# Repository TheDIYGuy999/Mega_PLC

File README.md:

# This is an Arduino based, modular Industrial PLC

## I have designed this PLC back in 2016. It is currently in use in an industrial screw tightening robot:
- 4 stepper motors for X, Y, Z axes and for screw tightening
- Matrix keyboard
- I2C LCD
- Digital I/O in use for pneumatic screw feeding system, buttons and reference switches

## Features:
- Works wit an Arduino MEGA or DUE
- DO board with 16 24V, 500mA PNP digital outputs, optoinsulated, short circuit protected @ about 900mA
- DI board with 16 24V PNP digital inputs, optoinsulated
- Stepper board for 4 stepper motors, torque adjustable via PWM
- Slot for communication board (I2C, CAN, SPI, 2x Serial)
- Slot for analog board (Analog in, PWM, DAC, I2C)

## This repo contains:
- Eagle schematics
- Eagle board files
- PDF schematics
- The analog and communication boards were made out of perfboard and are NOT included. Maybe someone other is interested in adding them.

## Pictures:

## Videos:
- I/O boards: https://www.youtube.com/watch?v=W2pYYh6aUXc
- First tepper tests: https://www.youtube.com/watch?v=gJDdZBuH5Kc

(c) 2016  TheDIYGuy999

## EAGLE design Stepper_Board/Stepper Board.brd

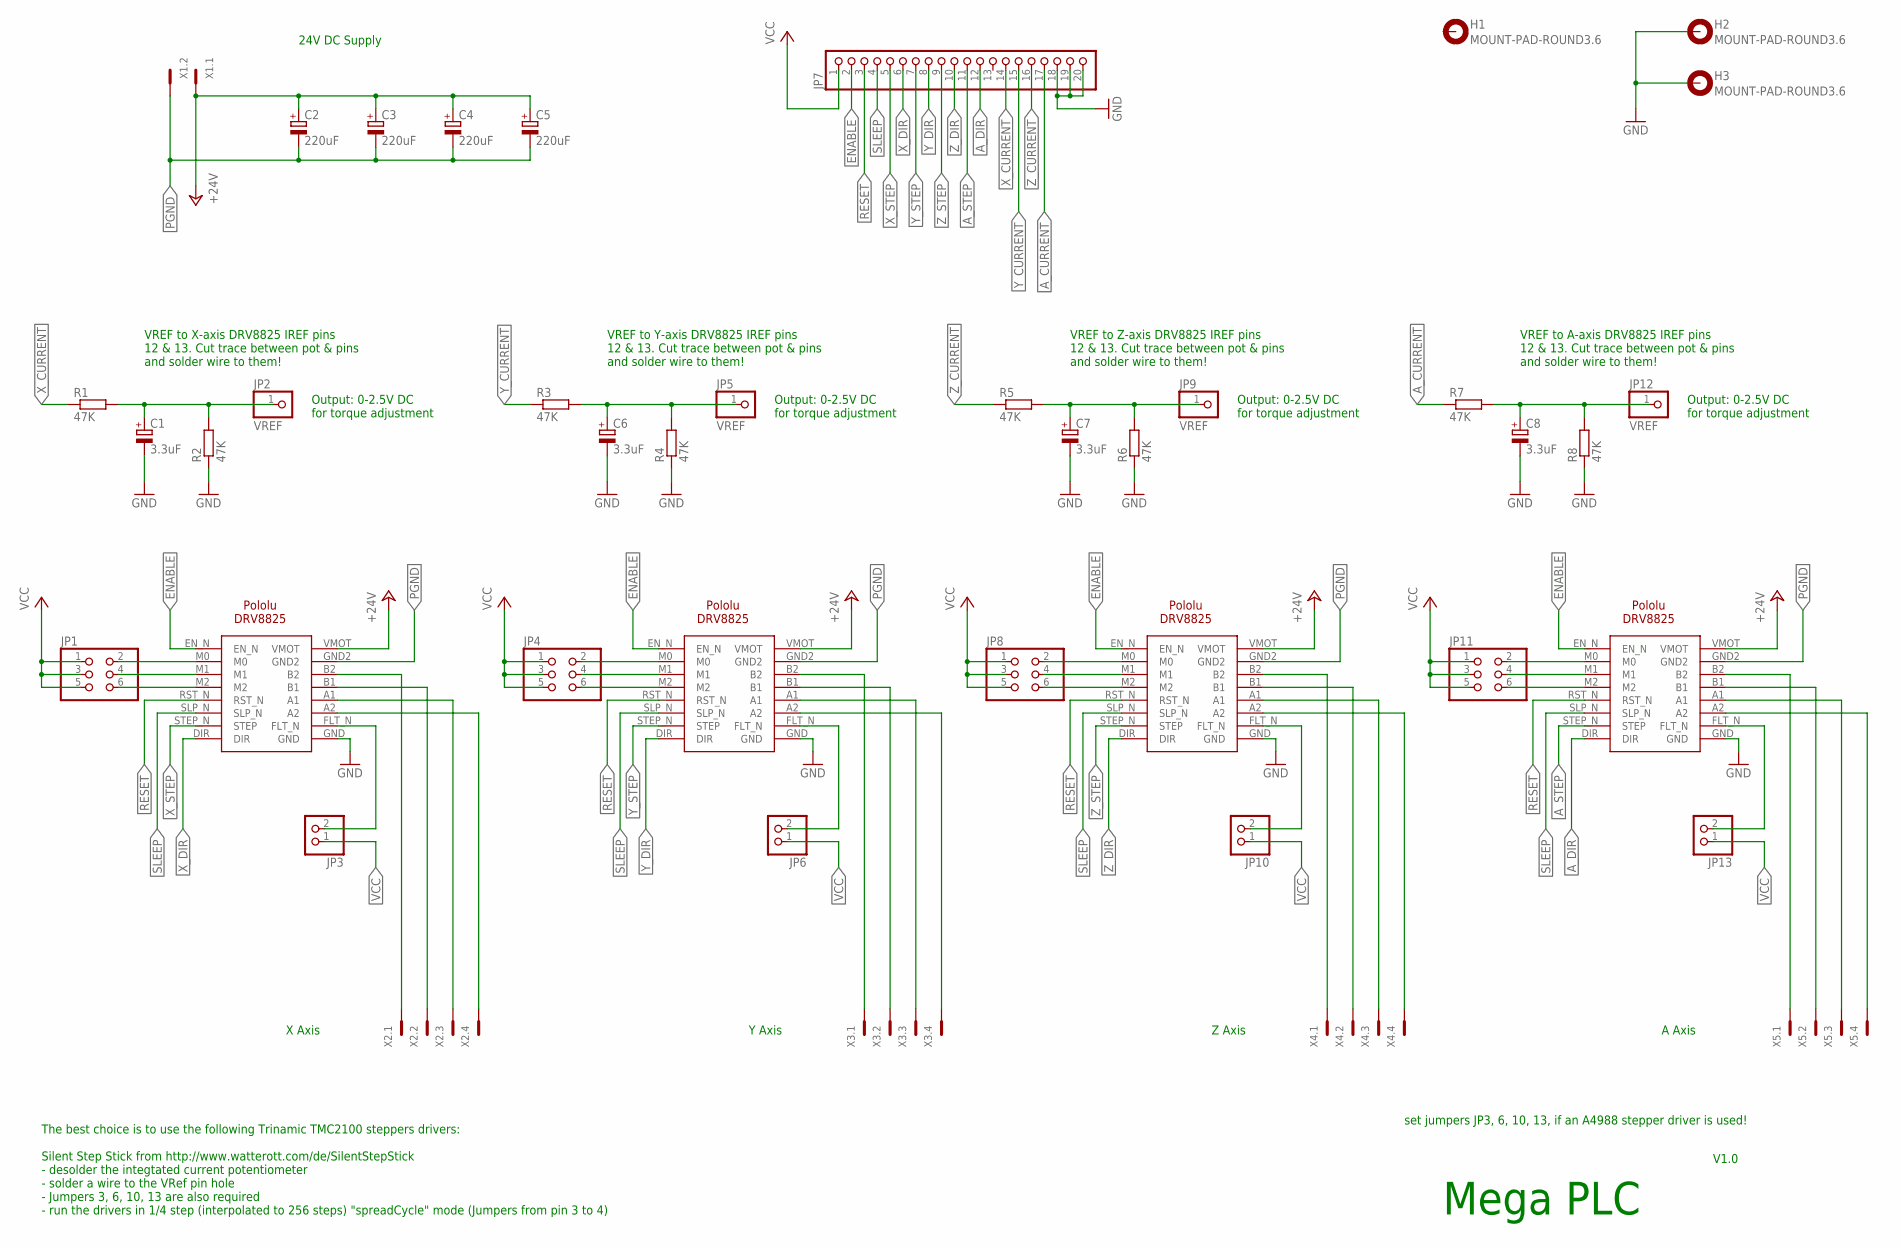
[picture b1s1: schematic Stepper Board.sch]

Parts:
C1, C6, C7, C8: 3.3uF; B45181A
C2, C3, C4, C5: 220uF; E5-10,5
H1, H2, H3: MOUNT-PAD-ROUND3.6; 3,6-PAD
JP1, JP4, JP8, JP11: PINHD-2X3; 2X03
JP2, JP5, JP9, JP12: VREF; 1X01
JP3, JP6, JP10, JP13: PINHD-1X2; 1X02
JP7: PINHD-1X20/90; 1X20/90
R1: 47K; 0204/7
R2, R4, R6, R8: 47K; 0207/15
R3, R5, R7: 47K; 0207/2V
U1, U2, U3, U4: POLOLU-DRV8825
X1: MC2
X2, X3, X4, X5: MC4

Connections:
+24V: C2.+, C3.+, C4.+, C5.+, U1.VMOT, U2.VMOT, U3.VMOT, U4.VMOT, X1.1
A_CURRENT: JP7.17, R7.1
A_DIR: JP7.12, U4.DIR
A_FLT: JP13.2, U4.FLT_N
A_STEP: JP7.11, U4.STEP_N (STEP)
ENABLE: JP7.2, U1.EN_N, U2.EN_N, U3.EN_N, U4.EN_N
GND: C1.-, C6.-, C7.-, C8.-, H2.B3,6, H3.B3,6, JP7.18, JP7.19, JP7.20, R2.1, R4.1, R6.1, R8.1, U1.GND, U2.GND, U3.GND, U4.GND
unnamed: U1.A2, X2.4
unnamed: U1.A1, X2.3
unnamed: JP1.2, U1.M0
unnamed: JP1.4, U1.M1
unnamed: JP1.6, U1.M2
unnamed: U1.B1, X2.2
unnamed: U1.B2, X2.1
unnamed: U2.A2, X3.4
unnamed: U2.A1, X3.3
unnamed: U2.B1, X3.2
unnamed: U2.B2, X3.1
unnamed: U3.A2, X4.4
unnamed: U3.A1, X4.3
unnamed: U3.B1, X4.2
unnamed: U3.B2, X4.1
unnamed: U4.A2, X5.4
unnamed: U4.A1, X5.3
unnamed: U4.B1, X5.2
unnamed: U4.B2, X5.1
unnamed: JP4.2, U2.M0
unnamed: JP4.4, U2.M1
unnamed: JP4.6, U2.M2
unnamed: JP8.2, U3.M0
unnamed: JP8.4, U3.M1
unnamed: JP8.6, U3.M2
unnamed: JP11.2, U4.M0
unnamed: JP11.4, U4.M1
unnamed: JP11.6, U4.M2
unnamed: C8.+, JP12.1, R7.2, R8.2
unnamed: C7.+, JP9.1, R5.2, R6.2
unnamed: C6.+, JP5.1, R3.2, R4.2
unnamed: C1.+, JP2.1, R1.2, R2.2
PGND: C2.-, C3.-, C4.-, C5.-, U1.GND2, U2.GND2, U3.GND2, U4.GND2, X1.2
RESET: JP7.3, U1.RST_N, U2.RST_N, U3.RST_N, U4.RST_N
SLEEP: JP7.4, U1.SLP_N, U2.SLP_N, U3.SLP_N, U4.SLP_N
VCC: JP1.1, JP1.3, JP1.5, JP3.1, JP4.1, JP4.3, JP4.5, JP6.1, JP7.1, JP8.1, JP8.3, JP8.5, JP10.1, JP11.1, JP11.3, JP11.5, JP13.1
X_CURRENT: JP7.14, R1.1
X_DIR: JP7.6, U1.DIR
X_FLT: JP3.2, U1.FLT_N
X_STEP: JP7.5, U1.STEP_N (STEP)
Y_CURRENT: JP7.15, R3.1
Y_DIR: JP7.8, U2.DIR
Y_FLT: JP6.2, U2.FLT_N
Y_STEP: JP7.7, U2.STEP_N (STEP)
Z_CURRENT: JP7.16, R5.1
Z_DIR: JP7.10, U3.DIR
Z_FLT: JP10.2, U3.FLT_N
Z_STEP: JP7.9, U3.STEP_N (STEP)

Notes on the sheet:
24V DC Supply
VREF to A-axis DRV8825 IREF pins 12 & 13. Cut trace between pot & pins and solder wire to them!
X Axis
Y Axis
Z Axis
A Axis
Output: 0-2.5V DC for torque adjustment
Mega PLC
set jumpers JP3, 6, 10, 13, if an A4988 stepper driver is used!
VREF to Z-axis DRV8825 IREF pins 12 & 13. Cut trace between pot & pins and solder wire to them!
VREF to Y-axis DRV8825 IREF pins 12 & 13. Cut trace between pot & pins and solder wire to them!
VREF to X-axis DRV8825 IREF pins 12 & 13. Cut trace between pot & pins and solder wire to them!
V1.0
The best choice is to use the following Trinamic TMC2100 steppers drivers: Silent Step Stick from http://www.watterott.com/de/SilentStepStick - desolder the integtated current potentiometer - solder a wire to the VRef pin hole - Jumpers 3, 6, 10, 13 are also required - run the drivers in 1/4 step (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

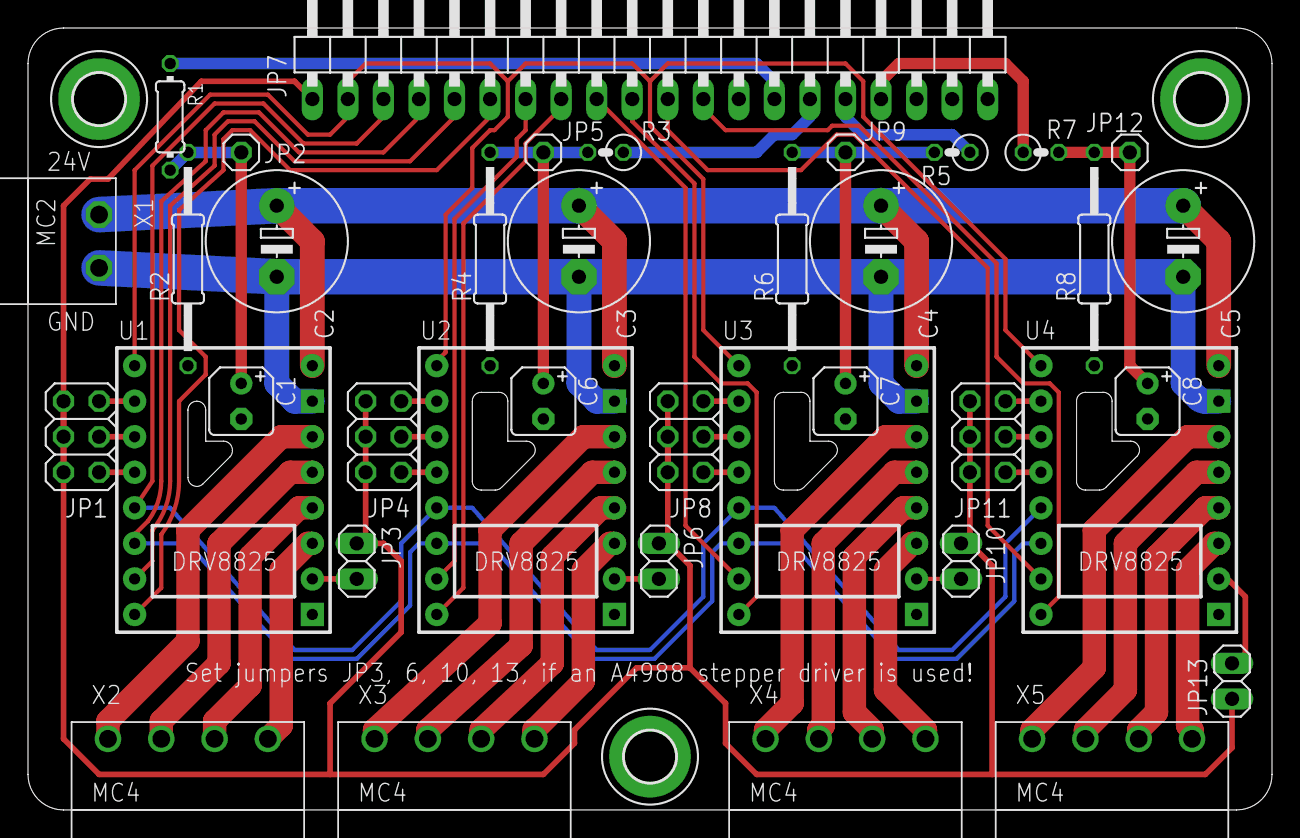
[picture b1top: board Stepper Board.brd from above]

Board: 2 copper layers, 88.9 x 55.9 mm, 41 parts (0 on the bottom side), 55 nets.

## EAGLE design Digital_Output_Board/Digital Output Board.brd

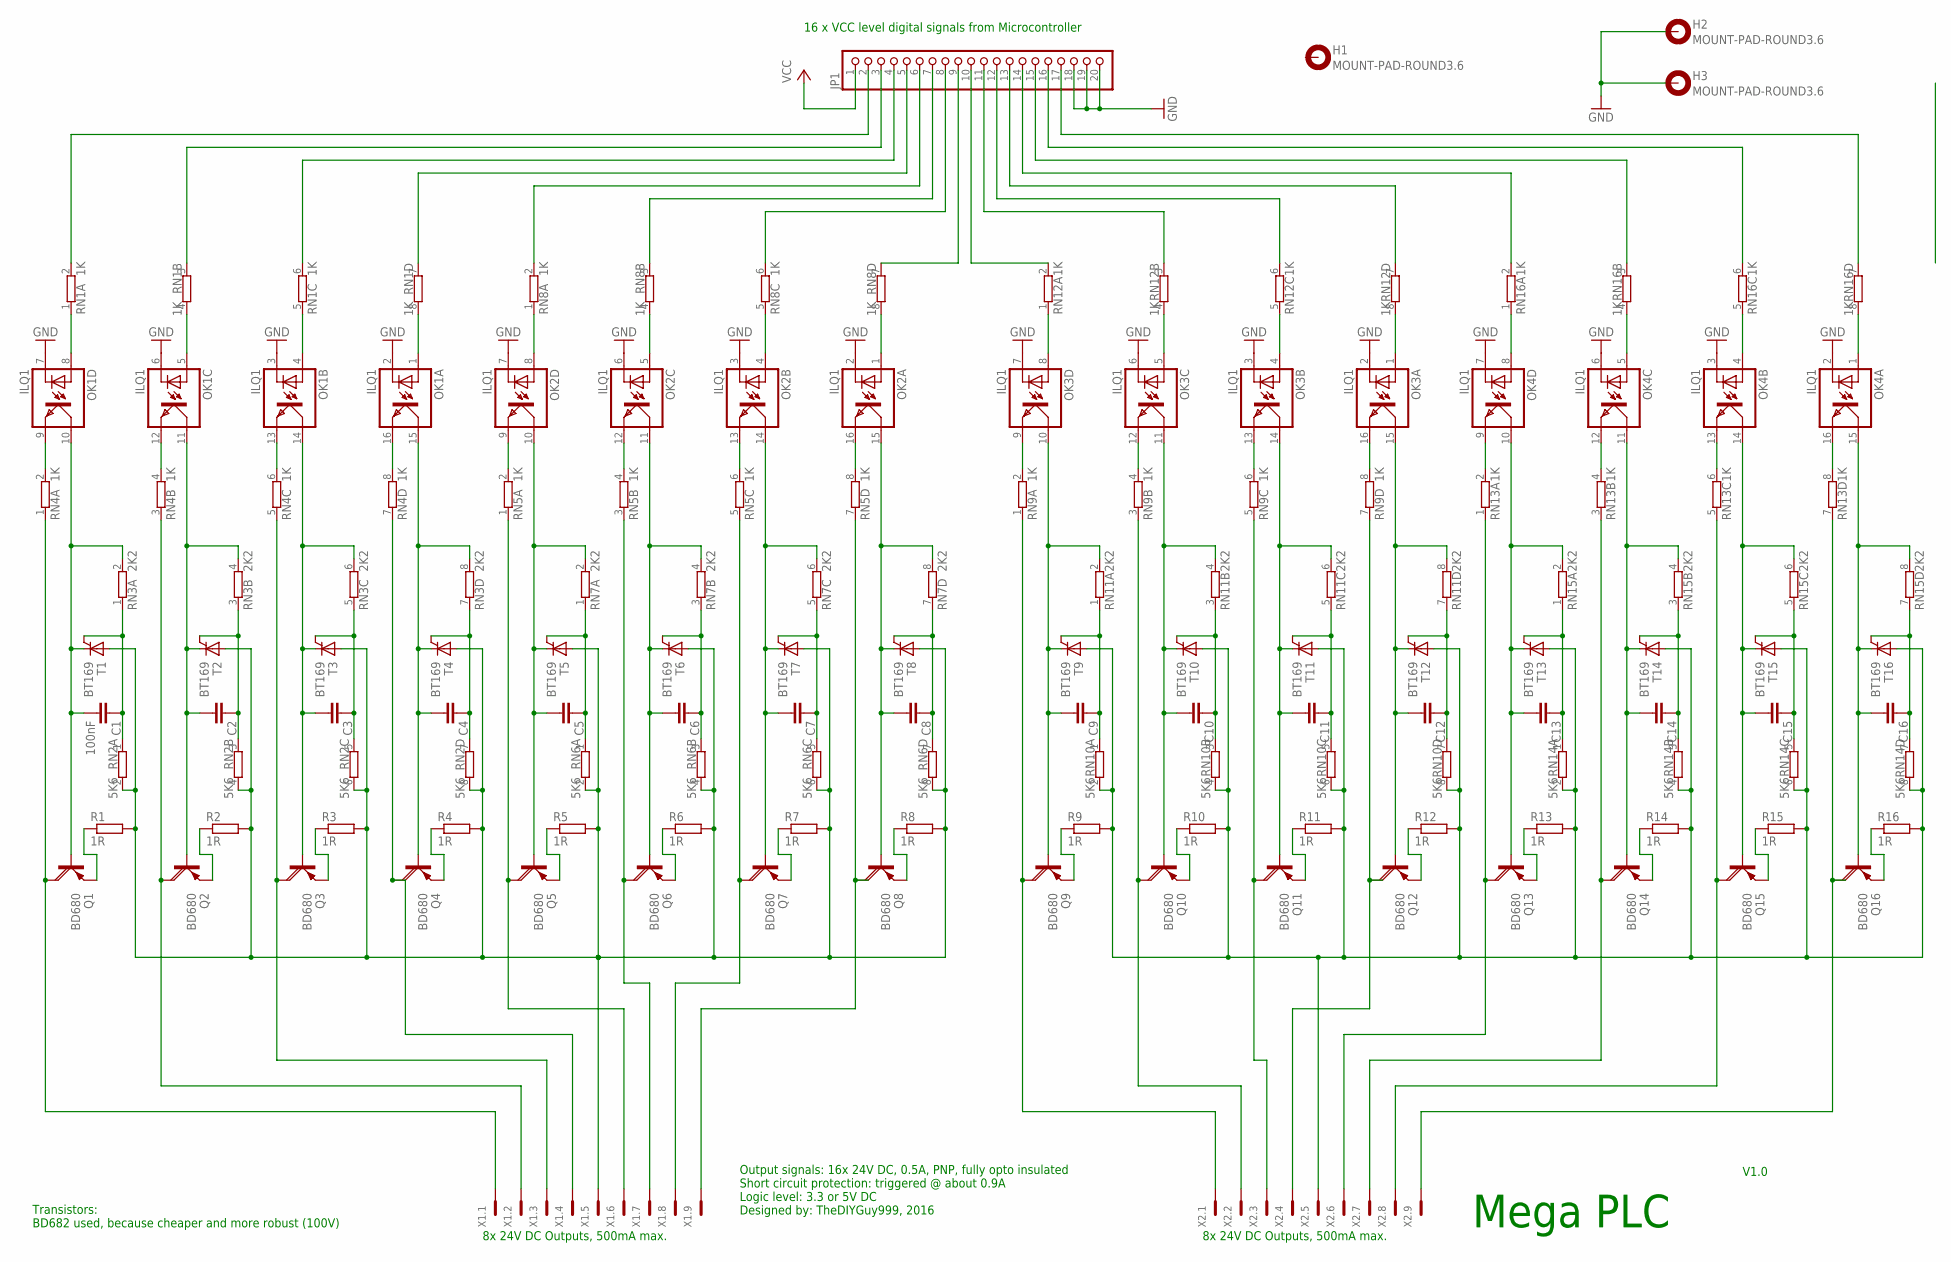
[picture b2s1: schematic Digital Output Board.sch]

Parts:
C1: 100nF; C025-024X044
C2, C3, C4, C5, C6, C7, C8, C9, C10, C11, C12, C13, C14, C15, C16: C-EU025-024X044; C025-024X044
H1, H2, H3: MOUNT-PAD-ROUND3.6; 3,6-PAD
JP1: PINHD-1X20/90; 1X20/90
OK1, OK2, OK3, OK4: ILQ1; DIL16
Q1, Q2, Q3, Q4, Q5, Q6, Q7, Q8, Q9, Q10, Q11, Q12, Q13, Q14, Q15, Q16: BD680; TO126AV
R1, R2, R3, R4, R5, R6, R7, R8, R9, R10, R11, R12, R13, R14, R15, R16: 1R; 0207/10
RN1, RN4, RN5, RN8, RN9, RN12, RN13, RN16: 1K; SIL8
RN2, RN6, RN10, RN14: 5K6; SIL8
RN3, RN7, RN11, RN15: 2K2; SIL8
T1, T2, T3, T4, T5, T6, T7, T8, T9, T10, T11, T12, T13, T14, T15, T16: BT169; TO92-2
X1, X2: MC9

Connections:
C+1: R1.2, R2.2, R3.2, R4.2, R5.2, R6.2, R7.2, R8.2, RN2.2, RN2.4 (2), RN2.6 (2), RN2.8 (2), RN6.2, RN6.4 (2), RN6.6 (2), RN6.8 (2), T1.A, T2.A, T3.A, T4.A, T5.A, T6.A, T7.A, T8.A, X1.5
C+2: R9.2, R10.2, R11.2, R12.2, R13.2, R14.2, R15.2, R16.2, RN10.2, RN10.4 (2), RN10.6 (2), RN10.8 (2), RN14.2, RN14.4 (2), RN14.6 (2), RN14.8 (2), T9.A, T10.A, T11.A, T12.A, T13.A, T14.A, T15.A, T16.A, X2.5
GND: H2.B3,6, H3.B3,6, JP1.18, JP1.19, JP1.20, OK1.2 (C), OK1.3 (C), OK1.6 (C), OK1.7 (C), OK2.2 (C), OK2.3 (C), OK2.6 (C), OK2.7 (C), OK3.2 (C), OK3.3 (C), OK3.6 (C), OK3.7 (C), OK4.2 (C), OK4.3 (C), OK4.6 (C), OK4.7 (C)
unnamed: Q1.E, R1.1
unnamed: OK1.8 (A), RN1.1
unnamed: OK1.5 (A), RN1.4 (2)
unnamed: OK1.4 (A), RN1.5 (1)
unnamed: OK1.1 (A), RN1.8 (2)
unnamed: JP1.2, RN1.2
unnamed: JP1.3, RN1.3 (1)
unnamed: JP1.4, RN1.6 (2)
unnamed: JP1.5, RN1.7 (1)
unnamed: OK1.9 (EMIT), RN4.2
unnamed: OK1.12 (EMIT), RN4.4 (2)
unnamed: OK1.13 (EMIT), RN4.6 (2)
unnamed: OK1.16 (EMIT), RN4.8 (2)
unnamed: C1.2, OK1.10 (COL), Q1.B, RN3.2, T1.C
unnamed: C1.1, RN2.1, RN3.1, T1.G
unnamed: Q1.C, RN4.1, X1.1
unnamed: Q2.C, RN4.3 (1), X1.2
unnamed: Q3.C, RN4.5 (1), X1.3
unnamed: Q4.C, RN4.7 (1), X1.4
unnamed: C2.2, OK1.11 (COL), Q2.B, RN3.4 (2), T2.C
unnamed: C3.2, OK1.14 (COL), Q3.B, RN3.6 (2), T3.C
unnamed: C4.2, OK1.15 (COL), Q4.B, RN3.8 (2), T4.C
unnamed: Q2.E, R2.1
unnamed: Q3.E, R3.1
unnamed: Q4.E, R4.1
unnamed: C2.1, RN2.3 (1), RN3.3 (1), T2.G
unnamed: C3.1, RN2.5 (1), RN3.5 (1), T3.G
unnamed: C4.1, RN2.7 (1), RN3.7 (1), T4.G
unnamed: JP1.6, RN8.2
unnamed: JP1.7, RN8.3 (1)
unnamed: JP1.8, RN8.6 (2)
unnamed: JP1.9, RN8.7 (1)
unnamed: OK2.8 (A), RN8.1
unnamed: OK2.4 (A), RN8.5 (1)
unnamed: OK2.5 (A), RN8.4 (2)
unnamed: OK2.1 (A), RN8.8 (2)
unnamed: OK2.9 (EMIT), RN5.2
unnamed: OK2.12 (EMIT), RN5.4 (2)
unnamed: OK2.13 (EMIT), RN5.6 (2)
unnamed: OK2.16 (EMIT), RN5.8 (2)
unnamed: C5.1, RN6.1, RN7.1, T5.G
unnamed: Q5.E, R5.1
unnamed: C5.2, OK2.10 (COL), Q5.B, RN7.2, T5.C
unnamed: Q5.C, RN5.1, X1.6
unnamed: Q6.C, RN5.3 (1), X1.7
unnamed: Q7.C, RN5.5 (1), X1.8
unnamed: Q8.C, RN5.7 (1), X1.9
unnamed: C6.2, OK2.11 (COL), Q6.B, RN7.4 (2), T6.C
unnamed: C7.2, OK2.14 (COL), Q7.B, RN7.6 (2), T7.C
unnamed: C8.2, OK2.15 (COL), Q8.B, RN7.8 (2), T8.C
unnamed: Q6.E, R6.1
unnamed: Q7.E, R7.1
unnamed: Q8.E, R8.1
unnamed: C6.1, RN6.3 (1), RN7.3 (1), T6.G
unnamed: C7.1, RN6.5 (1), RN7.5 (1), T7.G
unnamed: C8.1, RN6.7 (1), RN7.7 (1), T8.G
unnamed: OK3.8 (A), RN12.1
unnamed: OK3.4 (A), RN12.5 (1)
unnamed: OK3.5 (A), RN12.4 (2)
unnamed: OK3.1 (A), RN12.8 (2)
unnamed: OK3.9 (EMIT), RN9.2
unnamed: OK3.12 (EMIT), RN9.4 (2)
unnamed: OK3.13 (EMIT), RN9.6 (2)
unnamed: OK3.16 (EMIT), RN9.8 (2)
unnamed: C9.1, RN10.1, RN11.1, T9.G
unnamed: Q9.E, R9.1
unnamed: C9.2, OK3.10 (COL), Q9.B, RN11.2, T9.C
unnamed: Q9.C, RN9.1, X2.1
unnamed: Q10.C, RN9.3 (1), X2.2
unnamed: Q11.C, RN9.5 (1), X2.3
unnamed: Q12.C, RN9.7 (1), X2.4
unnamed: C10.2, OK3.11 (COL), Q10.B, RN11.4 (2), T10.C
unnamed: C11.2, OK3.14 (COL), Q11.B, RN11.6 (2), T11.C
unnamed: C12.2, OK3.15 (COL), Q12.B, RN11.8 (2), T12.C
unnamed: Q10.E, R10.1
unnamed: Q11.E, R11.1
unnamed: Q12.E, R12.1
unnamed: C10.1, RN10.3 (1), RN11.3 (1), T10.G
unnamed: C11.1, RN10.5 (1), RN11.5 (1), T11.G
unnamed: C12.1, RN10.7 (1), RN11.7 (1), T12.G
unnamed: OK4.8 (A), RN16.1
unnamed: OK4.4 (A), RN16.5 (1)
unnamed: OK4.5 (A), RN16.4 (2)
unnamed: OK4.1 (A), RN16.8 (2)
unnamed: OK4.9 (EMIT), RN13.2
unnamed: OK4.12 (EMIT), RN13.4 (2)
unnamed: OK4.13 (EMIT), RN13.6 (2)
unnamed: OK4.16 (EMIT), RN13.8 (2)
unnamed: C13.1, RN14.1, RN15.1, T13.G
unnamed: Q13.E, R13.1
unnamed: C13.2, OK4.10 (COL), Q13.B, RN15.2, T13.C
unnamed: Q13.C, RN13.1, X2.6
unnamed: Q14.C, RN13.3 (1), X2.7
unnamed: Q15.C, RN13.5 (1), X2.8
unnamed: Q16.C, RN13.7 (1), X2.9
unnamed: C14.2, OK4.11 (COL), Q14.B, RN15.4 (2), T14.C
unnamed: C15.2, OK4.14 (COL), Q15.B, RN15.6 (2), T15.C
unnamed: C16.2, OK4.15 (COL), Q16.B, RN15.8 (2), T16.C
unnamed: Q14.E, R14.1
unnamed: Q15.E, R15.1
unnamed: Q16.E, R16.1
unnamed: C14.1, RN14.3 (1), RN15.3 (1), T14.G
unnamed: C15.1, RN14.5 (1), RN15.5 (1), T15.G
unnamed: C16.1, RN14.7 (1), RN15.7 (1), T16.G
unnamed: JP1.10, RN12.2
unnamed: JP1.17, RN16.7 (1)
unnamed: JP1.16, RN16.6 (2)
unnamed: JP1.15, RN16.3 (1)
unnamed: JP1.14, RN16.2
unnamed: JP1.13, RN12.7 (1)
unnamed: JP1.12, RN12.6 (2)
unnamed: JP1.11, RN12.3 (1)
VCC: JP1.1

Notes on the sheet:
16 x VCC level digital signals from Microcontroller
8x 24V DC Outputs, 500mA max.
Transistors: BD682 used, because cheaper and more robust (100V)
Mega PLC
V1.0
Output signals: 16x 24V DC, 0.5A, PNP, fully opto insulated Short circuit protection: triggered @ about 0.9A Logic level: 3.3 or 5V DC Designed by: TheDIYGuy999, 2016

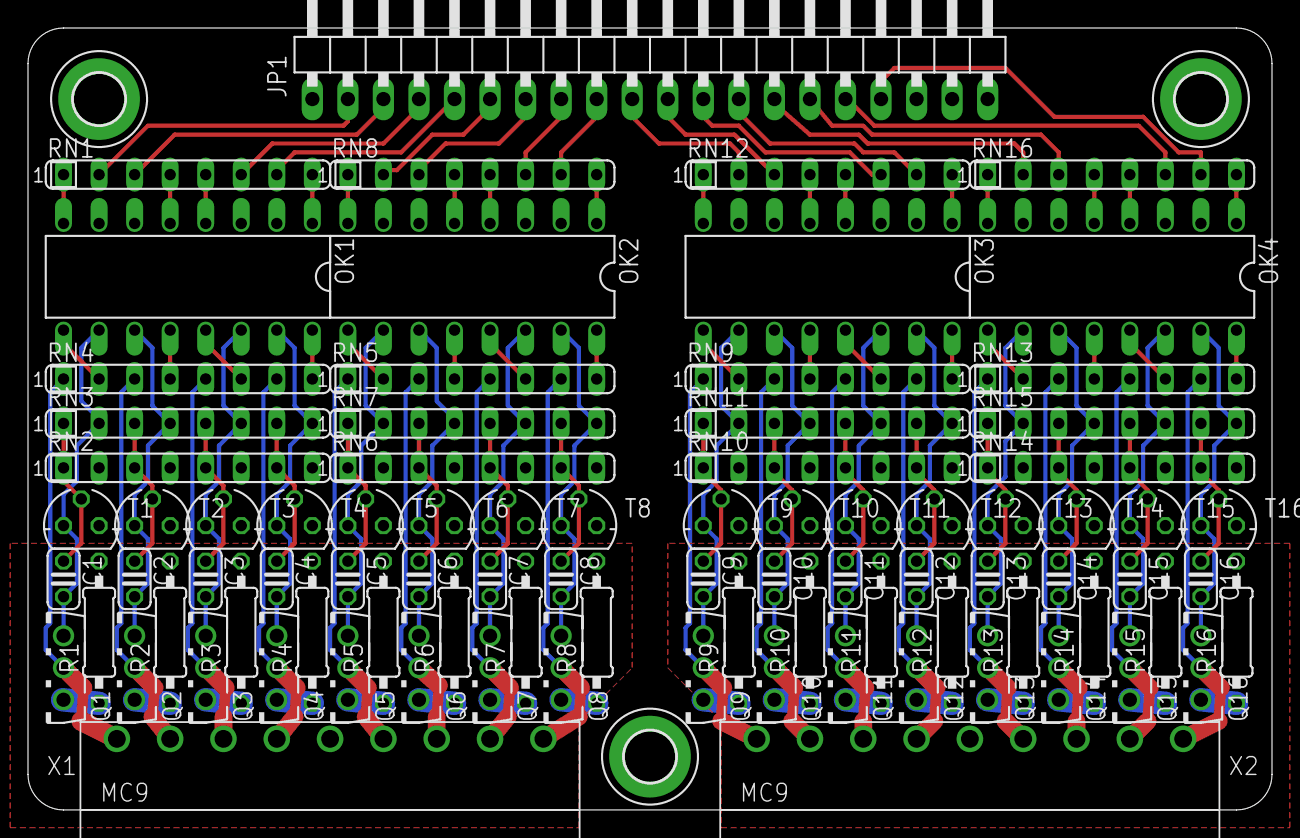
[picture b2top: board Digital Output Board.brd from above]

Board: 2 copper layers, 88.9 x 55.9 mm, 90 parts (0 on the bottom side), 115 nets.

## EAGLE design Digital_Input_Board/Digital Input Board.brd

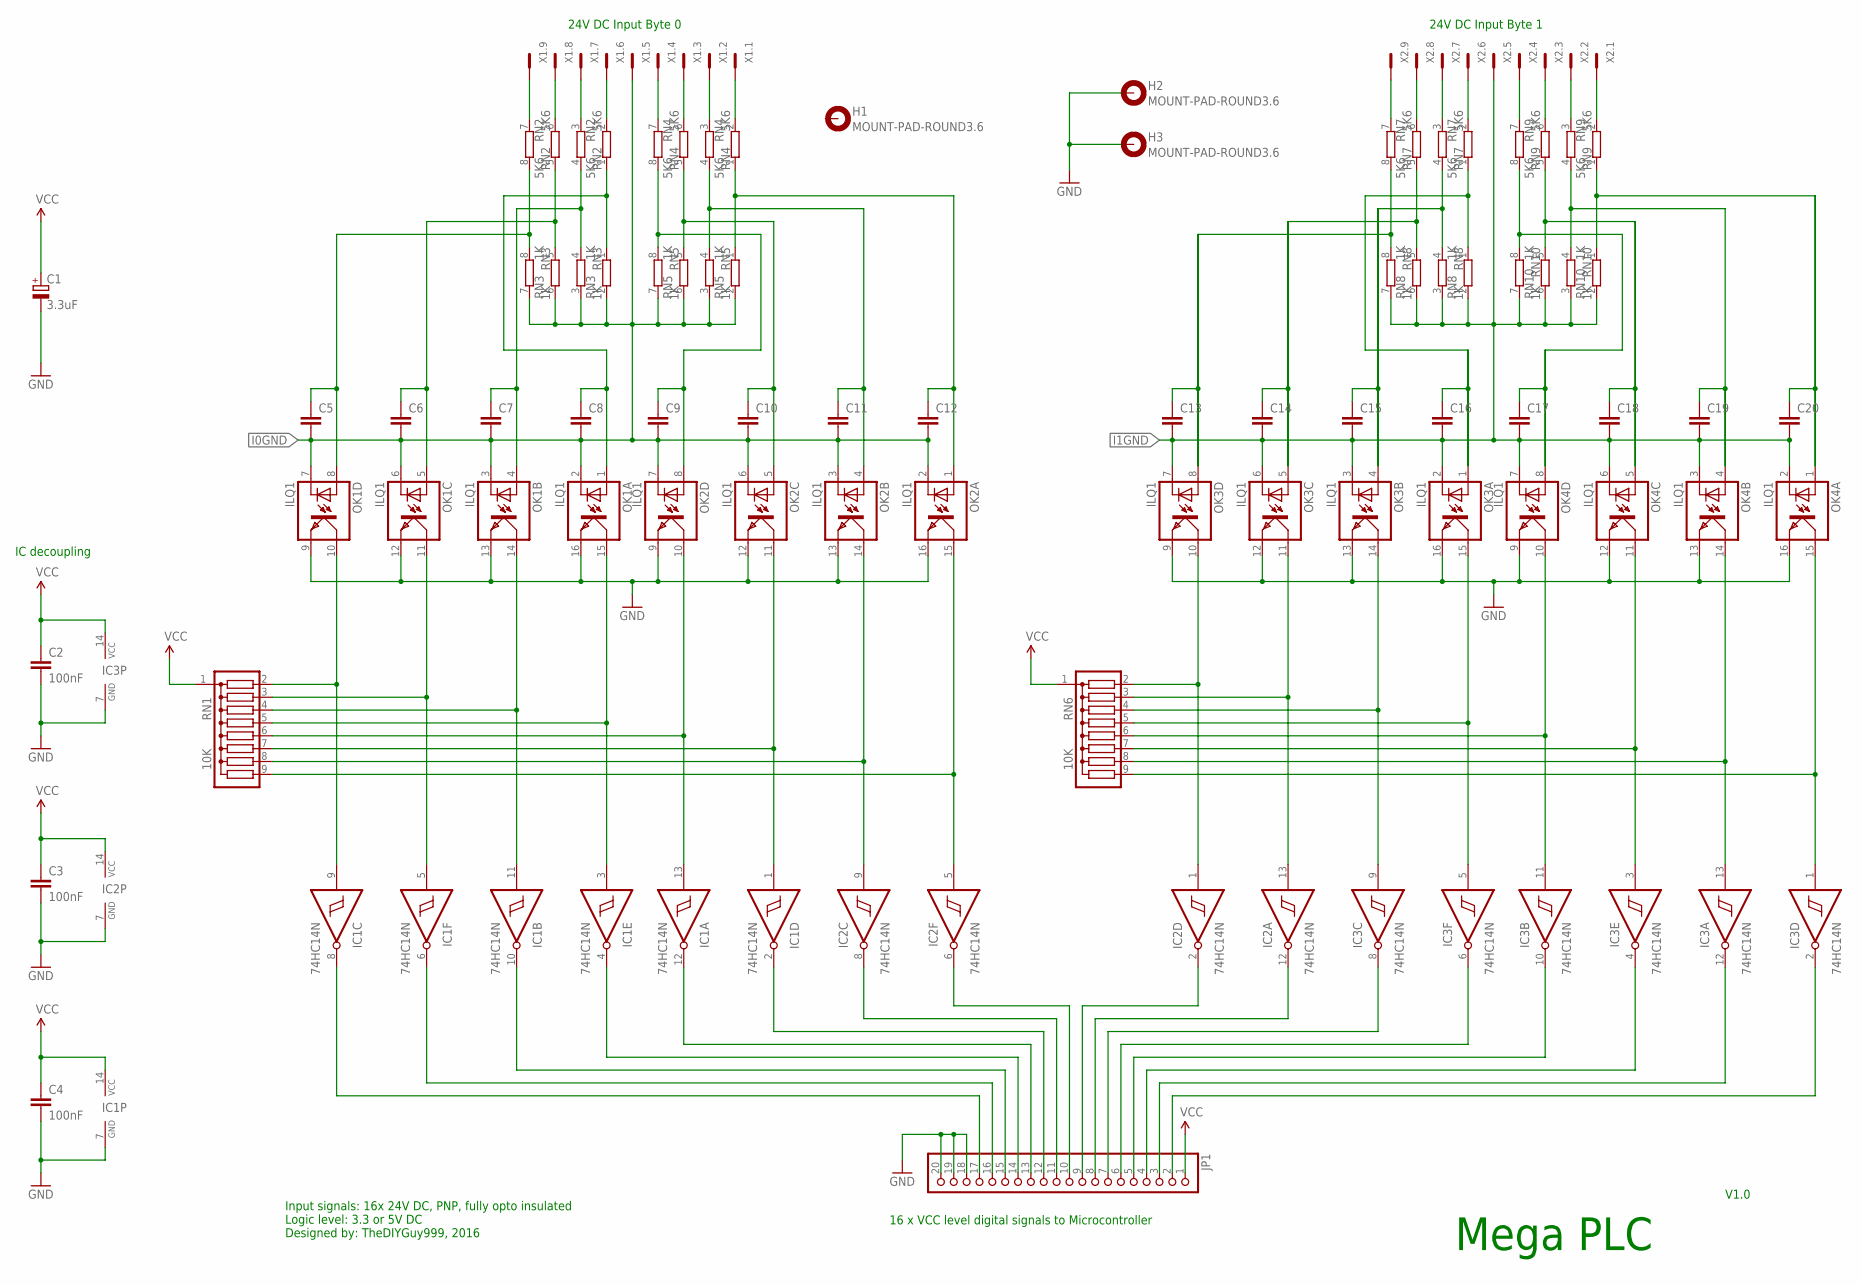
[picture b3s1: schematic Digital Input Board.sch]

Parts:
C1: 3.3uF; B45181A
C2, C3, C4: 100nF; C025-024X044
C5, C6, C7, C8, C9, C10, C11, C12, C13, C14, C15, C16, C17, C18, C19, C20: C-EUC0805K; C0805K
H1, H2, H3: MOUNT-PAD-ROUND3.6; 3,6-PAD
IC1, IC2, IC3: 74HC14N; DIL14
JP1: PINHD-1X20/90; 1X20/90
OK1, OK2, OK3, OK4: ILQ1; DIL16
RN1, RN6: 10K; SIL9
RN2, RN4, RN7, RN9: 5K6; SIL8
RN3, RN5, RN8, RN10: 1K; SIL8
X1, X2: MC9

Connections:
GND: C1.-, C2.2, C3.2, C4.2, H2.B3,6, H3.B3,6, IC1.7 (GND), IC2.7 (GND), IC3.7 (GND), JP1.18, JP1.19, JP1.20, OK1.9 (EMIT), OK1.12 (EMIT), OK1.13 (EMIT), OK1.16 (EMIT), OK2.9 (EMIT), OK2.12 (EMIT), OK2.13 (EMIT), OK2.16 (EMIT), OK3.9 (EMIT), OK3.12 (EMIT), OK3.13 (EMIT), OK3.16 (EMIT), OK4.9 (EMIT), OK4.12 (EMIT), OK4.13 (EMIT), OK4.16 (EMIT)
I0GND: C5.2, C6.2, C7.2, C8.2, C9.2, C10.2, C11.2, C12.2, OK1.2 (C), OK1.3 (C), OK1.6 (C), OK1.7 (C), OK2.2 (C), OK2.3 (C), OK2.6 (C), OK2.7 (C), RN3.2, RN3.3 (1), RN3.6 (2), RN3.7 (1), RN5.2, RN5.3 (1), RN5.6 (2), RN5.7 (1), X1.5
I1GND: C13.2, C14.2, C15.2, C16.2, C17.2, C18.2, C19.2, C20.2, OK3.2 (C), OK3.3 (C), OK3.6 (C), OK3.7 (C), OK4.2 (C), OK4.3 (C), OK4.6 (C), OK4.7 (C), RN8.2, RN8.3 (1), RN8.6 (2), RN8.7 (1), RN10.2, RN10.3 (1), RN10.6 (2), RN10.7 (1), X2.5
unnamed: RN9.7 (1), X2.4
unnamed: RN9.6 (2), X2.3
unnamed: RN9.3 (1), X2.2
unnamed: RN9.2, X2.1
unnamed: C20.1, OK4.1 (A), RN9.1, RN10.1
unnamed: C19.1, OK4.4 (A), RN9.4 (2), RN10.4 (2)
unnamed: C18.1, OK4.5 (A), RN9.5 (1), RN10.5 (1)
unnamed: C17.1, OK4.8 (A), RN9.8 (2), RN10.8 (2)
unnamed: IC3.1 (I), OK4.15 (COL), RN6.9
unnamed: IC3.13 (I), OK4.14 (COL), RN6.8
unnamed: IC3.3 (I), OK4.11 (COL), RN6.7
unnamed: RN7.2, X2.6
unnamed: IC2.13 (I), OK3.11 (COL), RN6.3
unnamed: RN7.7 (1), X2.9
unnamed: IC3.11 (I), OK4.10 (COL), RN6.6
unnamed: RN7.6 (2), X2.8
unnamed: RN7.3 (1), X2.7
unnamed: C16.1, OK3.1 (A), RN7.1, RN8.1
unnamed: C15.1, OK3.4 (A), RN7.4 (2), RN8.4 (2)
unnamed: C14.1, OK3.5 (A), RN7.5 (1), RN8.5 (1)
unnamed: C13.1, OK3.8 (A), RN7.8 (2), RN8.8 (2)
unnamed: IC3.5 (I), OK3.15 (COL), RN6.5
unnamed: IC3.9 (I), OK3.14 (COL), RN6.4
unnamed: C12.1, OK2.1 (A), RN4.1, RN5.1
unnamed: C11.1, OK2.4 (A), RN4.4 (2), RN5.4 (2)
unnamed: C10.1, OK2.5 (A), RN4.5 (1), RN5.5 (1)
unnamed: C9.1, OK2.8 (A), RN4.8 (2), RN5.8 (2)
unnamed: RN4.7 (1), X1.4
unnamed: RN4.6 (2), X1.3
unnamed: RN4.3 (1), X1.2
unnamed: RN4.2, X1.1
unnamed: IC2.1 (I), OK3.10 (COL), RN6.2
unnamed: IC2.5 (I), OK2.15 (COL), RN1.9
unnamed: IC2.9 (I), OK2.14 (COL), RN1.8
unnamed: IC1.1 (I), OK2.11 (COL), RN1.7
unnamed: RN2.2, X1.6
unnamed: RN2.6 (2), X1.8
unnamed: RN2.7 (1), X1.9
unnamed: RN2.3 (1), X1.7
unnamed: C8.1, OK1.1 (A), RN2.1, RN3.1
unnamed: C7.1, OK1.4 (A), RN2.4 (2), RN3.4 (2)
unnamed: C6.1, OK1.5 (A), RN2.5 (1), RN3.5 (1)
unnamed: C5.1, OK1.8 (A), RN2.8 (2), RN3.8 (2)
unnamed: IC1.13 (I), OK2.10 (COL), RN1.6
unnamed: IC1.3 (I), OK1.15 (COL), RN1.5
unnamed: IC1.11 (I), OK1.14 (COL), RN1.4
unnamed: IC1.5 (I), OK1.11 (COL), RN1.3
unnamed: IC1.9 (I), OK1.10 (COL), RN1.2
unnamed: IC3.2 (O), JP1.2
unnamed: IC3.12 (O), JP1.3
unnamed: IC3.4 (O), JP1.4
unnamed: IC3.10 (O), JP1.5
unnamed: IC3.6 (O), JP1.6
unnamed: IC3.8 (O), JP1.7
unnamed: IC2.12 (O), JP1.8
unnamed: IC2.2 (O), JP1.9
unnamed: IC2.6 (O), JP1.10
unnamed: IC2.8 (O), JP1.11
unnamed: IC1.2 (O), JP1.12
unnamed: IC1.12 (O), JP1.13
unnamed: IC1.4 (O), JP1.14
unnamed: IC1.10 (O), JP1.15
unnamed: IC1.6 (O), JP1.16
unnamed: IC1.8 (O), JP1.17
VCC: C1.+, C2.1, C3.1, C4.1, IC1.14 (VCC), IC2.14 (VCC), IC3.14 (VCC), JP1.1, RN1.1, RN6.1

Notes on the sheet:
Mega PLC
24V DC Input Byte 0
24V DC Input Byte 1
16 x VCC level digital signals to Microcontroller
IC decoupling
V1.0
Input signals: 16x 24V DC, PNP, fully opto insulated Logic level: 3.3 or 5V DC Designed by: TheDIYGuy999, 2016

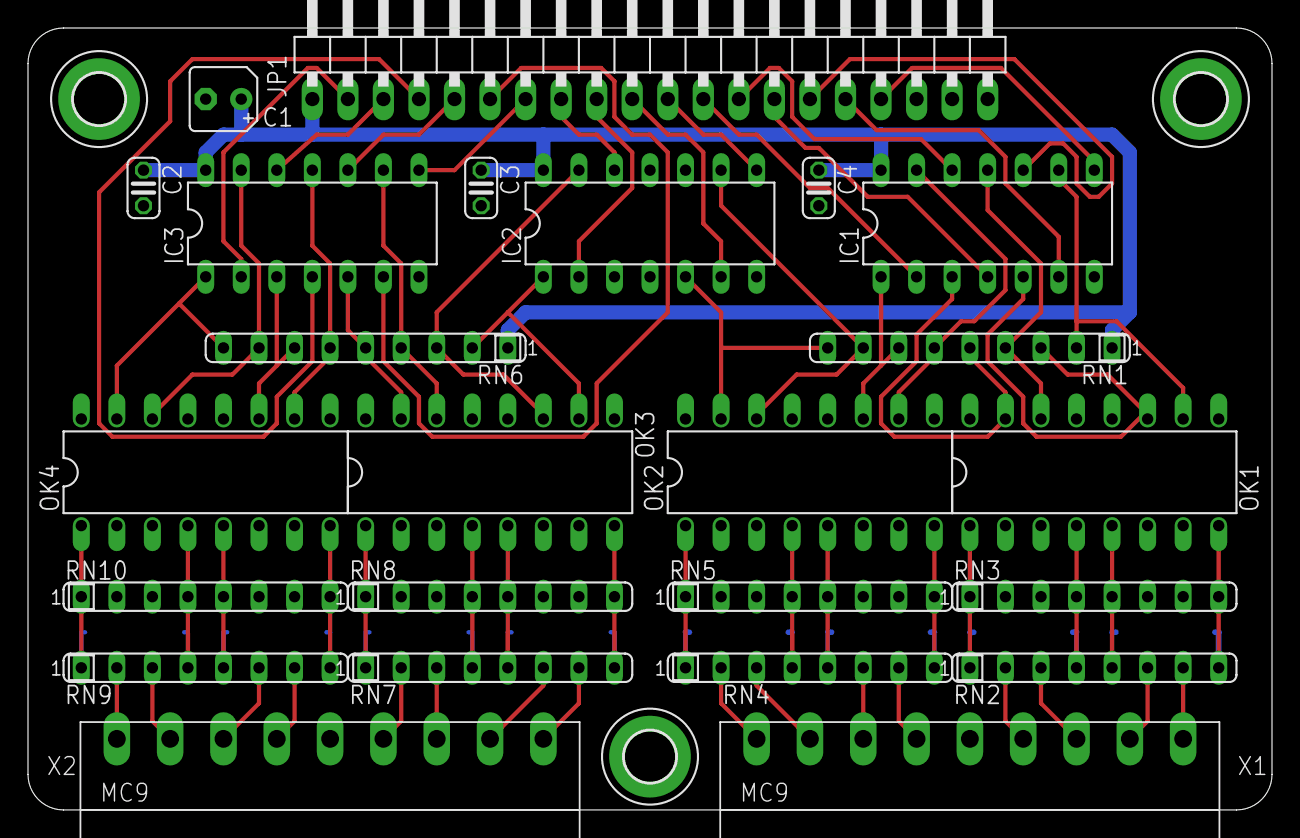
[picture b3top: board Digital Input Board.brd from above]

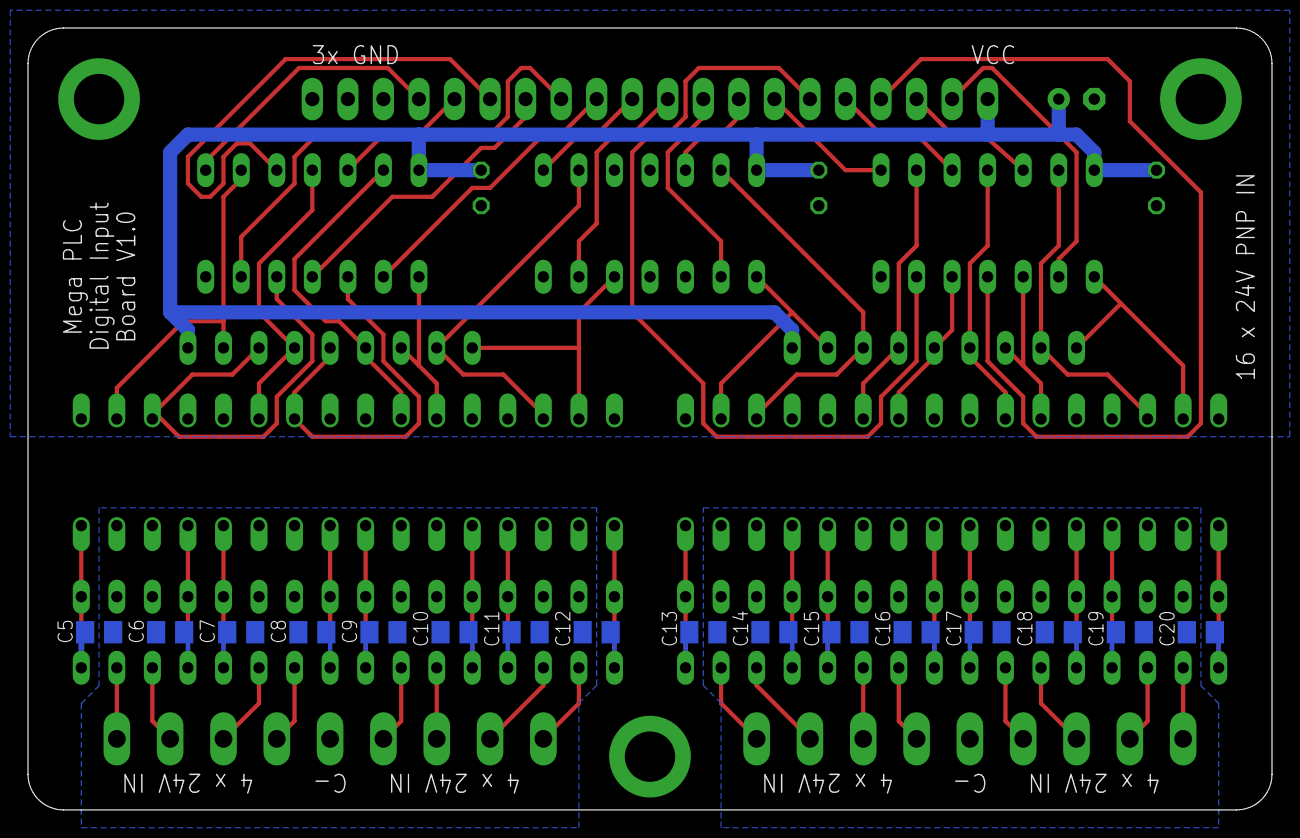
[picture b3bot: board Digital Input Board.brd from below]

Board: 2 copper layers, 88.9 x 55.9 mm, 43 parts (16 on the bottom side), 68 nets.

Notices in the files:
parts and their libraries:
SparkFun-Aesthetics: Licensing: Creative Commons ShareAlike 4.0 International - https://creativecommons.org/licenses/by-sa/4.0
